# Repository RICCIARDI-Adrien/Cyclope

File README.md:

# Cyclope

A little robot powered by a Raspberry Pi 3 A+, featuring a 8MPixel Raspberry Pi Camera V2 and a 360° lidar.  
A fast WiFi connection allows to remote control the robot while displaying camera real-time full HD video stream.  
A tailored Buildroot Linux distribution runs the software, controlled through WiFi through an embedded web server.

## Hardware

PCB has been designed using KiCad 5.1.5 and has been ported to KiCad 6. All manufacturing files are available from [Release](https://github.com/RICCIARDI-Adrien/Cyclope/releases) page.  
A PDF version of the schematic is also provided.

## Software

Robot's Raspberry Pi is powered by a tailored [Buildroot](https://buildroot.org) Linux distribution.

### Getting sources

Clone the repository and the submodules all in the row :
```
git clone --recurse-submodules https://github.com/RICCIARDI-Adrien/Cyclope
```

### Building

Enter repository directory, clean previous build (if needed) and generate image :
```
cd Cyclope/Software/buildroot
make distclean
make BR2_EXTERNAL=$(realpath ..)/cyclope cyclope_defconfig
make
```

Generated image to burn to a SD card is `Cyclope/Software/buildroot/output/images/sdcard.img`.

## Mechanical

Chassis is made of two overlaid 3mm-thick steel plates.  
See [Mechanical_Dimensions.odg](Chassis/Mechanical_Dimensions.odg) file for additional design information.  
Provide the `Chassis.dxf` file from [Release](https://github.com/RICCIARDI-Adrien/Cyclope/releases) page to a metal laser cutting service.

## Supply parts

See `Bill_Of_Material.csv` file from [Release](https://github.com/RICCIARDI-Adrien/Cyclope/releases) page for PCB parts. All other needed mechanical and electrical parts are listed below.

### Electrical

* 2x servomotor : [Feetech FS5113R](https://www.gotronic.fr/art-servomoteur-fs5113r-25841.htm)
* 40-pin flat cable : [Amphenol FC40150-0](https://fr.farnell.com/amphenol/fc40150-0/cordon-2-54mm-f-f-150mm-40voies/dp/2217617)
* Battery holder : [EM8](https://www.gotronic.fr/art-coupleur-8-piles-lr6-em8-5718.htm), isolate apparent contacts but battery holder ones with adhesive tape to prevent them from touching chassis spacers

### Mechanical

* Front castor wheel : [Guitel 55031100](https://fr.rs-online.com/web/p/roulettes-industrielles/3064300).
* 2x servomotor support : [ASB01](https://www.gotronic.fr/art-support-de-servos-asb01-11637.htm).
* 2x servomotor wheel : [FS5103R-W](https://www.gotronic.fr/art-roue-pour-servomoteur-fs5103r-25857.htm).
* 2x front board flat angle bracket : NFLE2012-20.
* 21x chassis plates M4x40 hex female spacer : [Ettinger 05.04.401](https://fr.farnell.com/ettinger/05-04-401/entretoise-m4x40-vzk/dp/1466794).
* 4x M2x20 screw to attach camera to front board (use three nuts per screw). Using such long screws allow to further protect the camera.
* 12x M2 nut.
* 4x M2.5x25 screws to attach Raspberry Pi to chassis bottom plate (use three nets per screw).
* 12x M2.5 nut.
* 18x M3x10 screw :
  * 8x to attach both servomotors to their support.
  * 4x to attach the two supports to chassis bottom plate.
  * 4x to attach front board flat angle brackets to chassis bottom plate.
  * 2x to attach front board to flat angle brackets.
* 4x M3x15 screw to attach motherboard to chassis bottom plate (use three nuts per screw).
* 30x M3 nut.
* 47x M4x10 screw :
  * 21x to attach female spacers to chassis bottom plate.
  * 4x to attach castor wheel to chassis bottom plate.
  * 1x to prevent battery pack from escaping from robot bottom.
  * 21x to attach chassis top plate to chassis.
* 5x M4 nut.
* Use flat washers of appropriate dimensions if desired.

## Photo gallery

### Castor wheel

### Servomotor, wheel and support

### Chassis

### PCB

### Motherboard

PCB has been soldered by hands (resistors array part was missing, I used normal 0805 resistors) :

A big capacitor has been added to keep battery voltage stable when a lot of current is required :

### Front board

With Raspberry Pi Camera V2 mounted :

### Assembled electronic boards

### Assembled robot

### Update for version 1.1 adding a 360° lidar

Chassis top plate with lidar holes :

Lidar assembled on chassis top plate :

Motherboard PCB with lidar support :

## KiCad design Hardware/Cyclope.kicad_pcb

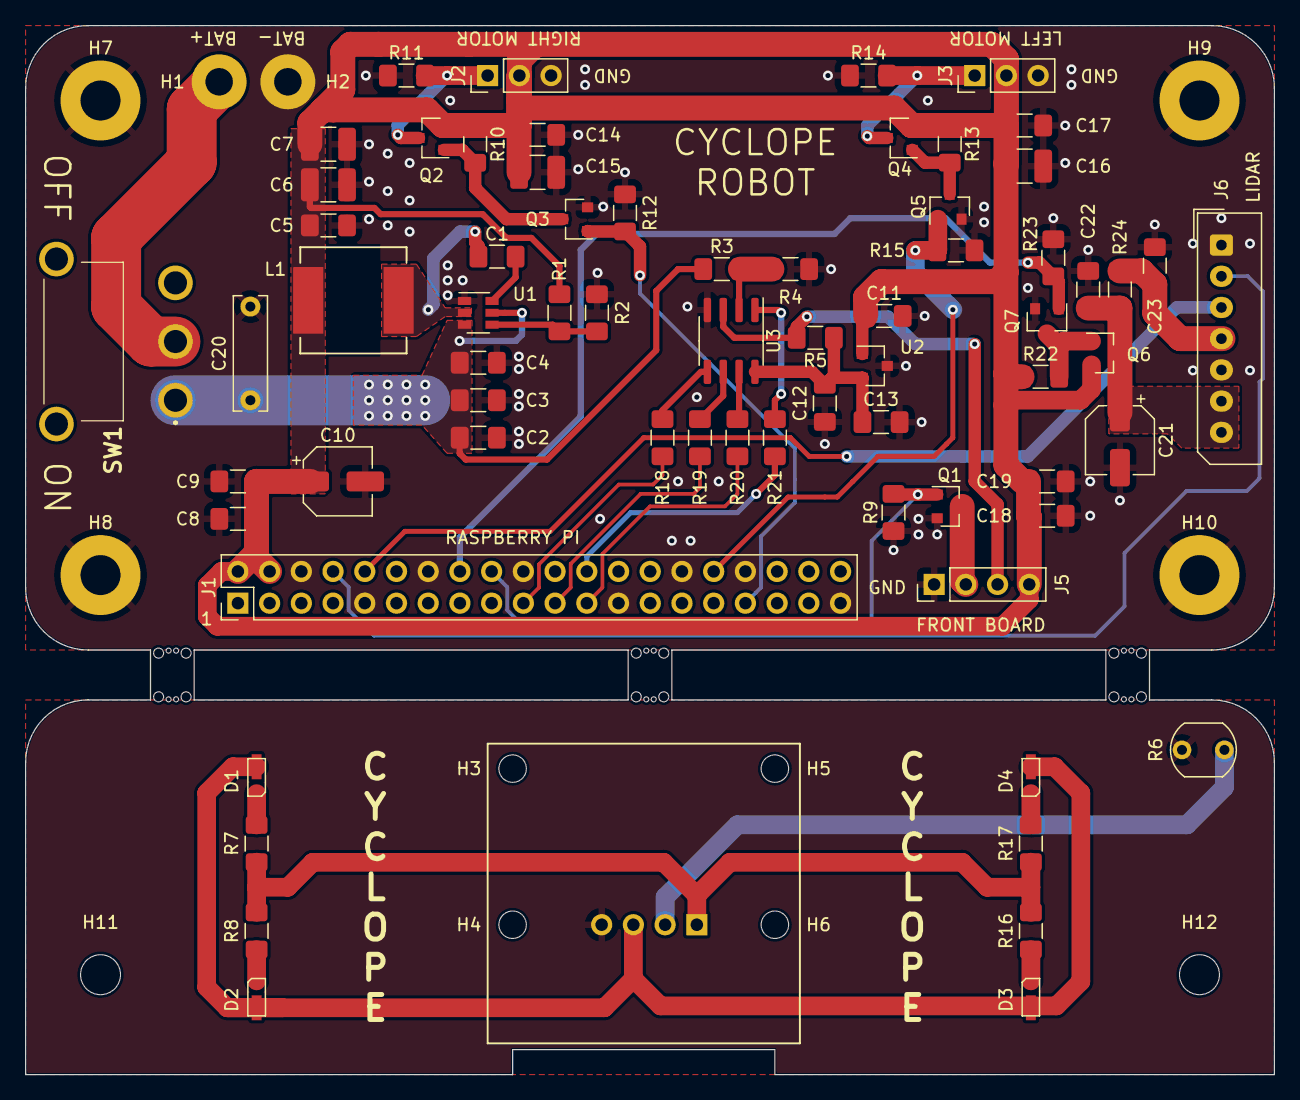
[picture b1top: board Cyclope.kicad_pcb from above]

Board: 2 copper layers, 100.0 x 84.0 mm, 88 parts (1 on the bottom side), 40 nets.

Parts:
BAT1: MP000303; Supply_Part
BT1, BT2, BT3, BT4, BT5, BT6: BreakTab; Break_Tab
C1, C4, C8, C11, C12, C18, C23: 100n; C_1206_3216Metric_Pad1.42x1.75mm_HandSolder
C2, C3, C5, C22: 10u; C_1206_3216Metric_Pad1.42x1.75mm_HandSolder
C6, C7, C15, C16: 22u; C_1210_3225Metric_Pad1.42x2.65mm_HandSolder
C9, C13, C14, C17, C19: 2.2u; C_1206_3216Metric_Pad1.42x1.75mm_HandSolder
C10, C21: 47u; CP_Elec_5x5.4
C20: 4700u; C_Rect_L9.0mm_W2.5mm_P7.50mm_MKT
D1, D2, D3, D4: 158301250
H1: BATTERY+; MountingHole_2.2mm_M2_Pad
H2: BATTERY-; MountingHole_2.2mm_M2_Pad
H3, H4, H5, H6: Camera; MountingHole_2.2mm_M2
H7, H8, H9, H10: Motherboard; MountingHole_3.2mm_M3_Pad
H11, H12: Front_Board; MountingHole_3.2mm_M3
J1: M20-9762042; PinHeader_2x20_P2.54mm_Vertical
J2: Motor_2; PinHeader_1x03_P2.54mm_Vertical
J3: Motor_1; PinHeader_1x03_P2.54mm_Vertical
J4, J5: Front; PinHeader_1x04_P2.54mm_Vertical
J6: 22-03-5075; Molex_SPOX_5267-07A_1x07_P2.50mm_Vertical
L1: IHLP3232DZER3R3M01
Q1, Q3, Q5, Q7: DMG3414U; SOT-23
Q2, Q4, Q6: DMG2301L; SOT-23
R1: 54.9K; R_1206_3216Metric_Pad1.42x1.75mm_HandSolder
R2, R3, R5, R9, R10, R12, R13, R15, R22, R23: 10K; R_1206_3216Metric_Pad1.42x1.75mm_HandSolder
R4: 2.7K; R_1206_3216Metric_Pad1.42x1.75mm_HandSolder
R6: LDR07; R_LDR_5.1x4.3mm_P3.4mm_Vertical
R7, R8, R11, R14, R16, R17: 100; R_1206_3216Metric_Pad1.42x1.75mm_HandSolder
R18, R19, R20, R21: 10; R_1206_3216Metric_Pad1.42x1.75mm_HandSolder
R24: 0; R_1206_3216Metric_Pad1.42x1.75mm_HandSolder
SW1: 1101M2S3ABE2; 1101M2S3AQE2
U1: TPS565208DDC; SOT-23-6
U2: NCP51460SN33T1G; SOT-23
U3: MCP3002; SOIC-8_3.9x4.9mm_P1.27mm

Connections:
+3.3VA: C12.1, C13.1, R5.1, U2.2, U3.8
+5V: C5.2, C6.2, C7.2, C8.2, C9.2, C10.1, C11.1, C14.2, C15.2, C16.2, C17.2, C18.2, C19.2, J1.2, J1.4, J2.2, J3.2, J5.4, L1.2, Q2.2, Q4.2, Q6.2, R1.1, R10.1, R13.1, R22.1, U2.1
+5VD: J4.1, R7.1, R8.1, R16.1, R17.1
ADC_SPI_CS: J1.24, R21.2
ADC_SPI_MISO: J1.21, R19.1
ADC_SPI_MOSI: J1.19, R18.1
ADC_SPI_SCK: J1.23, R20.1
BATTERY+: C2.2, C3.2, C4.2, C20.1, R3.1, SW1.1, U1.3, U1.5
FRONT_BOARD_LDR: J5.3, R5.2, U3.3
FRONT_BOARD_LEDS: J1.18, Q1.1, R9.2
GND: C2.1, C3.1, C4.1, C5.1, C6.1, C7.1, C8.1, C9.1, C10.2, C11.2, C12.2, C13.2, C14.1, C15.1, C16.1, C17.1, C18.1, C19.1, C20.2, C21.2, C22.1, C23.2, H2.1, H7.1, H8.1, H9.1, H10.1, J1.6, J1.9, J1.14, J1.20, J1.25, J1.30, J1.34, J1.39, J2.3, J3.3, J5.1, J6.1, J6.5, Q1.2, Q3.2, Q5.2, Q7.2, R2.2, R4.2, R9.1, R11.1, R12.2, R14.1, R15.2, R23.2, U1.1, U2.3, U3.4
GNDD: J4.4, R6.2
LIDAR_ENABLE: J1.16, Q7.1, R23.1
LIDAR_UART_RX: J1.8, J6.2
LIDAR_UART_TX: J1.10, J6.3
unnamed: C1.1, L1.1, U1.2
unnamed: C1.2, U1.6
unnamed: C21.1, C22.2, J6.6, J6.7, Q6.3, R24.2
unnamed: C23.1, J6.4, R24.1
unnamed: D1.1, D2.1, D3.1, D4.1, J4.3
unnamed: D1.2, R7.2
unnamed: D2.2, R8.2
unnamed: D3.2, R16.2
unnamed: D4.2, R17.2
unnamed: H1.1, SW1.2
unnamed: J1.32, Q5.1, R15.1
unnamed: J1.33, Q3.1, R12.1
unnamed: J2.1, Q2.3, R11.2
unnamed: J3.1, Q4.3, R14.2
unnamed: J4.2, R6.1
unnamed: J5.2, Q1.3
unnamed: Q2.1, Q3.3, R10.2
unnamed: Q4.1, Q5.3, R13.2
unnamed: Q6.1, Q7.3, R22.2
unnamed: R1.2, R2.1, U1.4
unnamed: R3.2, R4.1, U3.2
unnamed: R18.2, U3.5
unnamed: R19.2, U3.6
unnamed: R20.2, U3.7
unnamed: R21.1, U3.1

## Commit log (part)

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2020-07-27 Initial commit. Added .gitignore.
2020-07-27 [Hardware] Started schematic. Added power supply sheet.
2020-07-28 [Hardware] Started ADC schematic sheet. Added ADC, voltage regulator and battery voltage sensing.
2020-07-28 [Hardware] Connected ADC to Raspberry Pi through SPI bus.
2020-07-28 [Hardware] Added 158301250 led footprint.
2020-07-28 [Hardware] Added Raspberry Pi mounting holes to schematic.
2020-07-28 [Software] Added Buildroot 2020.05.1 as git submodule.
2020-07-28 [Software] Selected musl C library.
2020-07-28 Added firmware building information to README.md.
2020-07-28 [Software] Removed root password until development is finished.
2020-07-28 [Software] Moved system logs to data partition, so they can survive a firmware update.
2020-07-28 [Software] Added automatic mounting of data partition on boot.
2020-07-28 [Software] Enabled WiFi driver.
2020-07-28 [Software] Enabled WPA supplicant package.
2020-07-28 [Software] Added automatic creation of wpa_supplicant configuration directory on data partition.
2020-07-29 [Software] Enabled socat package.
2020-07-29 [Software] Added automatic mounting of boot partition on system boot.
2020-07-29 [Software] Moved Dropbear configuration to data partition.
2020-07-29 [Software] Discarded socat messages telling that client disconnected.
2020-07-29 [Hardware] Added front board dimensions to PCB.
2020-07-29 [Hardware] Added two more leds for a better night lighting.
2020-07-29 [Hardware] Added camera holes and a cut for camera cable to front board PCB.
2020-08-16 [Software][PC application] Added empty Qt project.
2020-08-16 [Chassis] Removed battery blocking screw hole from top plate as it is used only by bottom plate.
2020-08-16 [Hardware] Fixed a Edge.Cuts layer line width in PCB.
2020-08-16 [Chassis] Moved construction drawings to a dedicated layer, so it is easy to remove the constrution layer before exporting to manufacturer.
2020-08-16 [Hardware] Improved component names placement on motherboard PCB.
2020-08-16 [Chassis] Added Raspberry Pi 3 A+ dimensions.
2020-08-16 [Hardware] Routed front board PCB.
2020-08-16 [Hardware] Routed motherboard left motor transistors.
2020-08-16 [Hardware] Positionned all motherboard parts on PCB.
2020-08-16 [Chassis] Added battery pack position and fixing holes.
2020-08-16 [Hardware] Set final motherboard PCB dimensions, positionned ADC parts on PCB.
2020-08-16 [Chassis] Added bottom plate top and sides.
2020-08-16 Added some mechanical parts to README.md.
2020-08-16 [Hardware] Fixed bad footprints and duplicated break tab footprints.
2020-08-16 [Chassis] Started chassis design. Added motor block.
2020-08-16 [Chassis] Added bottom plate fixations for components, added top plate.
2020-08-16 [Chassis] Added and positionned motherboard.
2020-08-16 [Hardware] Routed part of ADC, routed Raspberry Pi power supply.
2020-08-16 [Software][Cyclope controller] Added logging system.
2020-08-16 [Hardware] Added larger tracks and a return path for motherboard PCB +5V.
2020-08-16 [Chassis] Added front board angle brackets (not positionned for now).
2020-08-16 [Chassis] Added bottom plate fixation holes.
2020-08-16 [Chassis] Removed two minuscule cicles that were confusing metal laser cutting service.
2020-08-16 [Software][Cyclope controller] Started motor module implementation. Added motor PWM channels export.
2020-08-16 [Software][PC application] Added configuration module, it allows to store configuration data to an INI file.
2020-08-16 [Software] Added all history checking out to Buildroot GitHub Action in order to make sources retrieval work.
2020-08-16 [Software][PC application] Started communication protocol module implementation.
2020-08-17 [Software][PC application] Added configuration module initialization and uninitialization.
2020-08-17 [Software][PC application] Added empty FormMainMenu.
2020-08-17 [Software][PC application] Added FormMainMenu empty user interface.
2020-08-17 Added missing link to GitHub Releases page in README.md hardware section.
2020-08-17 [Software][Cyclope controller] Added Network::waitForProgramExecutionRequest() method.
2020-08-17 [Software] Removed unused variables from upgrade script.
2020-08-17 [Software] Used an environment variable to specify Qt version in PC application GitHub Actions workflow.
2020-08-17 [Software] Added Linux build instructions to PC application GitHub Actions workflow.
2020-08-17 [Software] Used NMAKE to build PC application in GitHub Actions workflow Windows job.
2020-08-18 [Software][Cyclope controller] Started communication protocol commands implementation. Added 'set motion' command beginning.
2020-08-18 [Software][PC application] Added 'set robot motion' communication protocol command.
2020-08-18 [Software][PC application] Added robot motion control using keyboard direction keys to FormRemoteControl.
2020-08-18 [Software][Cyclope controller] Started light module implementation. Added leds GPIO initialization.
2020-08-18 [Software][PC application] Added 'set light enabled' communication protocol command.
2020-08-19 Told in README.md that a PDF version of the schematic is provided in GitHub release page.
2020-08-19 Added assembled bottom chassis pictures to README.md.
2020-08-21 [Software][Cyclope controller] Added an init script starting cyclope-controller program as a daemon.
2020-08-21 [Software] Disabled wpa_supplicant as robot will now create its own WiFi access point.
2020-08-22 [Software] Added an init script starting hostapd on boot.
2020-08-22 [Software] Ignored PC application build artifacts using a more generic rule.
2020-08-22 [Software][PC application] Added 'backward left' and 'backward right' robot motions support to FormRemoteControl.
2020-08-23 [Software][Cyclope controller] Added 'power off' communication protocol command support.
2020-08-24 [Software] Declared MCP3002 ADC in device tree.
2020-08-24 [Software][Cyclope controller] Moved Motor sysfs method to dedicated Sysfs namespace.
2020-08-26 Added front board pictures to README.md.
2020-08-26 Added links redirection to GitHub Actions when clicking a build badge in README.md.
2020-08-26 [Hardware] Replaced in schematic hard to find resistors array using 2012 package by classic 1206 discrete resistors.
2020-08-26 [Hardware] Inverted Raspberry Pi UART RX and TX in PCB.
2020-08-26 Added Cyclope picture at the beginning of README.md.
2020-08-26 [Software][Cyclope controller] Added 'get battery voltage' communication protocol command support.
2020-08-30 [Software][Cyclope controller] Improved battery voltage value stability by using a moving average.
2020-09-20 [Software][PC application] Added initial support for robot video displaying in FormRemoteControl.
2020-09-20 [Software][PC application] Added a confirmation message when powering robot off to FormMainMenu.
2020-10-11 [Software][Cyclope controller] Added communication protocol 'start AI program' command support.
2020-10-15 [Software] Added OpenCV 4 package (copied from Buildroot OpenCV 3 package).
2020-10-17 [Software] Added V4L2 VideoCore kernel modules loading to make '/dev/video0' node appear.
2020-10-17 [Software] Removed now useless OpenCV 4 custom Buildroot package.
2020-10-18 [Software][Cyclope controller] Added more V4L / OpenCV dependencies selection to Buildroot package.
2020-10-18 [Software][Cyclope controller] Started tennis ball detection AI algorithm. Some false positives are still detected.
2020-10-18 [Software][Cyclope controller] Added basic motors control to tennis ball following AI program.
2020-10-18 [Software][PC application] Added empty FormStartProgram.
2020-10-18 [Software][PC application] Allowed to double-click on an AI program name to run it in FormStartProgram.
2020-10-19 [Software][PC application] Added battery level displaying to FormExecuteProgram.
2020-10-30 [Software][PC application] Started Windows build script implementation. Application can currently be successfully built and dependencies are deployed.
2020-10-31 [Software] Bumped Buildroot version to 2020.08.1.
2021-02-06 [Resources] Added some lidar measurements.
2021-02-06 [Hardware] Added lidar connector 3D model.
2021-02-15 [Software] Disabled tty on AMA0 to dedicate serial port to lidar.
2021-02-15 [Software][Cyclope controller] Added Lidar::setEnabled() method.
2021-03-07 [Software][Cyclope controller] Added lidar serial port initialization and communication test.
2021-03-14 [Software][Cyclope controller] Added retrieval of lidar measure distances (they are currently not correlated to measured angle).
2021-03-20 [Software][Cyclope controller] Used SDK algorithm to compute lidar angles. This is currently a dirty proof of concept.
2021-03-20 [Software][Cyclope controller] Made lidar distance measures available from Lidar namespace global array.
2021-03-20 [Software][Cyclope controller] Started the 'wander with no goal' artificial intelligence program. It is currently a lidar test.
2021-03-20 [Software][Cyclope controller] Added software shutdown of the lidar module before turning its power supply off.
2021-03-21 [Hardware] Mirrored lidar connector as connector datasheet numbering does not match lidar datasheet numbering.
2021-03-28 [Software] Bumped kernel version to 5.10.
2021-03-28 [Software][Cyclope controller] Turned off lidar and light in addition of stopping motors when exiting an artificial intelligence program execution.
2021-04-05 [Software][Cyclope controller] Replaced 'wander with no goal' program logic by a state machine to be able to create a more complex backward direction moving sequence.
2021-04-06 [Software][PC application] Added 'set streaming camera' communication protocol command support.
2021-04-06 [Software][Cyclope controller] Used the same algorithm than backward navigation for 'wander with no goal' AI program forward navigation.
2021-11-07 [Software] Bumped Buildroot version to 2021.08.1.
2022-09-04 Told in README.md that PCB has been ported to KiCad 6.
2022-09-06 Added MIT license.
2024-12-01 [Software] Doubled the Buildroot FAT partition to accomodate for the increasing amount of device tree overlays.
    Also set a fixed size for the A/B partitions, this is cleaner than hardcoding offsets.
2024-12-02 [Software][Cyclope controller] Added the foundations for a web server interface. The server does nothing for now.
2024-12-04 [Software][Cyclope controller] Statically allocated the web server pages.
2024-12-05 [Software][Cyclope controller] Added to the manual control web page the JavaScript logic to generate HTTP POST requests when a keyboard key is pressed.
2024-12-08 [Software][Cyclope controller] Ported the PC application robot motion control algorithm to the web server.
2024-12-12 [Software][Cyclope controller] Added the 'get battery voltage' command to the web server and added the battery status to the manual control web page.
2024-12-14 [Software][Cyclope controller] Added a base class to derive the AI programs from.
2024-12-14 [Software][Cyclope controller] Added the retrieval of the URL arguments when the server services a HTTP 'GET' request.
2024-12-15 [Software][Cyclope controller] Avoid memory leak in the web server if a page content generation failed.
2024-12-15 [Software][Cyclope controller] Stopped the currently running AI program when exiting the 'execute program' web page.
2024-12-15 [Software][Cyclope controller] Added the displaying of the battery status to the AI program execution web page.
2024-12-18 [Software][Cyclope controller] Displayed a confirmation dialog when powering the robot off.
2024-12-18 [Software][Cyclope controller] Ported the 'follow tennis ball' AI program to the new architecture.
2024-12-18 [Software][PC application] Removed the PC application as it has been superseeded by the embedded web server.
2024-12-18 [Software] Moved Buildroot and the external tree directly to the Software directory.
